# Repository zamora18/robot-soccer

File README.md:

Robot Soccer - Team 5: Chicken McThuggets
=========================================

#### Background

Robot Soccer is a competition held each year where teams from all over the world build robots based on motion control, artificial intelligence (AI) and strategy, computer vision, and mechanical design. These robots compete in an autonomous soccer game as regulated by two independent organizations: RoboCup and FIRA. Both organizations were founded in 1997 and have continued to gain international popularity from its fans.

The Electrical and Computer Engineering Department at Brigham Young University also hosts a smaller-scale Robot Soccer competition. This competition was built to be a senior project for undergraduates and is the amalgamation of many sub-disciplines within ECEn. This is the third iteration of this particular senior project based on the ODROID and RoboClaw motor controllers. The BYU competition requires that ten Robot Soccer teams will create two soccer-playing robots each.

#### Our Robots

  - Nugget
  - Nugget v2.0
  - Fry

#### Resources

  - [Our Wiki](https://github.com/zamora18/robot-soccer/wiki)
  - [BYU Class Wiki](http://rwbclasses.groups.et.byu.net/doku.php?id=robot_soccer:2016:start)

#### Contact

  - [Parker Lusk](https://github.com/plusk01), motion control
  - [Chris Frame](https://github.com/cwframe), vision
  - [Troy Ellis](https://github.com/robo-hobojoe), hardware
  - [Jake Zamora](https://github.com/zamora18), AI and strategy

To see what has become of us, view our [credits](https://www.youtube.com/watch?v=zJYsS5C2Bes)!

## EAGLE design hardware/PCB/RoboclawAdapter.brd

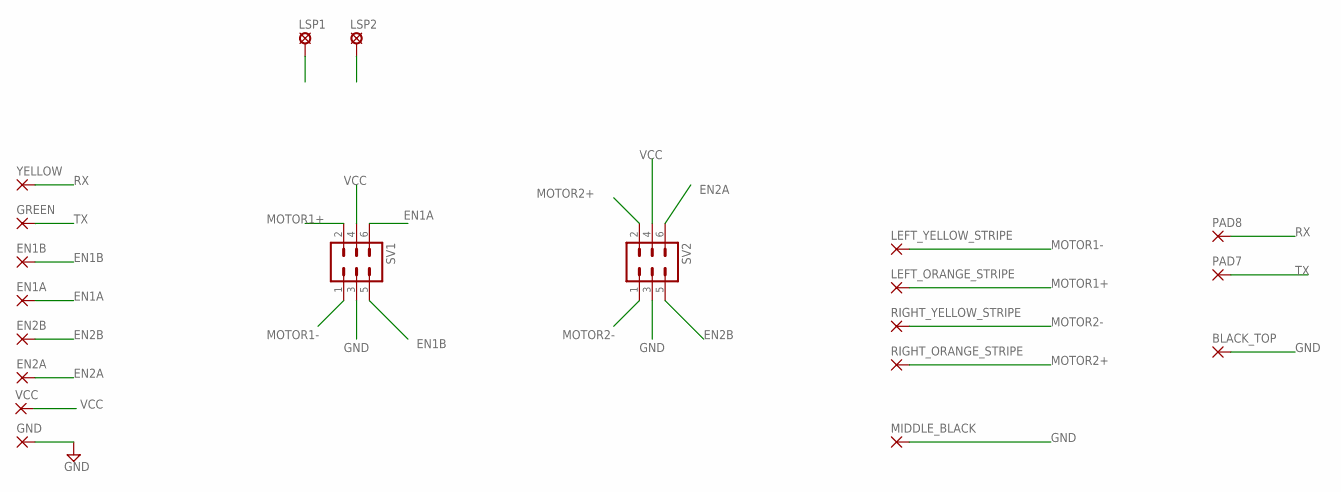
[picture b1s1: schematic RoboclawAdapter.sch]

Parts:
BLACK_TOP: 2,54/0,9
EN1A, EN1B, EN2A, EN2B: 2,54/0,9
GND: 2,54/0,9
GREEN: 2,54/0,9
LEFT_ORANGE_STRIPE: 2,54/0,9
LEFT_YELLOW_STRIPE: 2,54/0,9
LSP1, LSP2: SE14
MIDDLE_BLACK: 2,54/0,9
PAD7, PAD8: 2,54/0,9
RIGHT_ORANGE_STRIPE: 2,54/0,9
RIGHT_YELLOW_STRIPE: 2,54/0,9
SV1, SV2: MA03-2
VCC: 2,54/0,9
YELLOW: 2,54/0,9

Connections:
EN1A: EN1A.1, SV1.6
EN1B: EN1B.1, SV1.5
EN2A: EN2A.1, SV2.6
EN2B: EN2B.1, SV2.5
GND: BLACK_TOP.1, GND.1, MIDDLE_BLACK.1, SV1.3, SV2.3
MOTOR1+: LEFT_ORANGE_STRIPE.1, SV1.2
MOTOR1-: LEFT_YELLOW_STRIPE.1, SV1.1
MOTOR2+: RIGHT_ORANGE_STRIPE.1, SV2.2
MOTOR2-: RIGHT_YELLOW_STRIPE.1, SV2.1
RX: PAD8.1, YELLOW.1
TX: GREEN.1, PAD7.1
VCC: SV1.4, SV2.4, VCC.1
VCC12: LSP1.MP, LSP2.MP

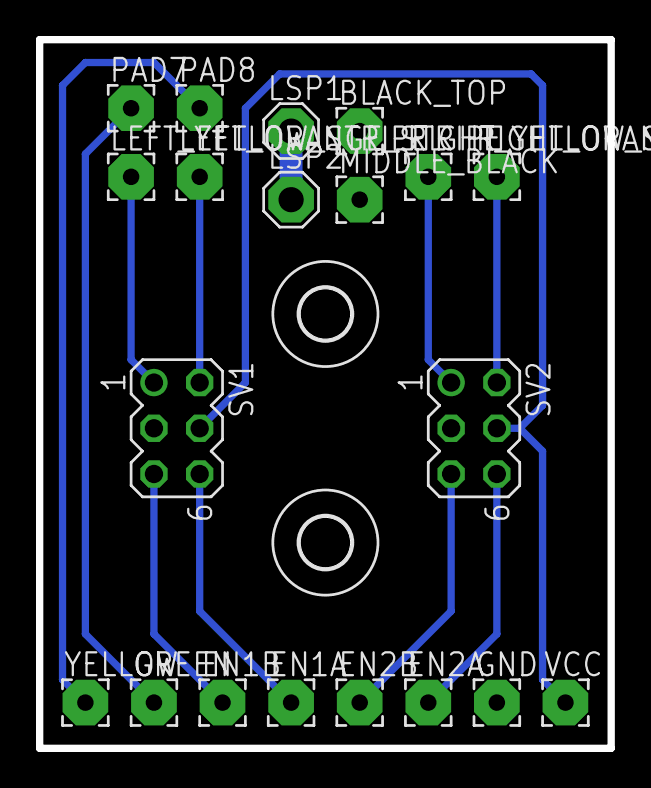
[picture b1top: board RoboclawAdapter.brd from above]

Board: 2 copper layers, 31.8 x 39.4 mm, 22 parts (0 on the bottom side), 13 nets.

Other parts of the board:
U$1, U$2: 2,8

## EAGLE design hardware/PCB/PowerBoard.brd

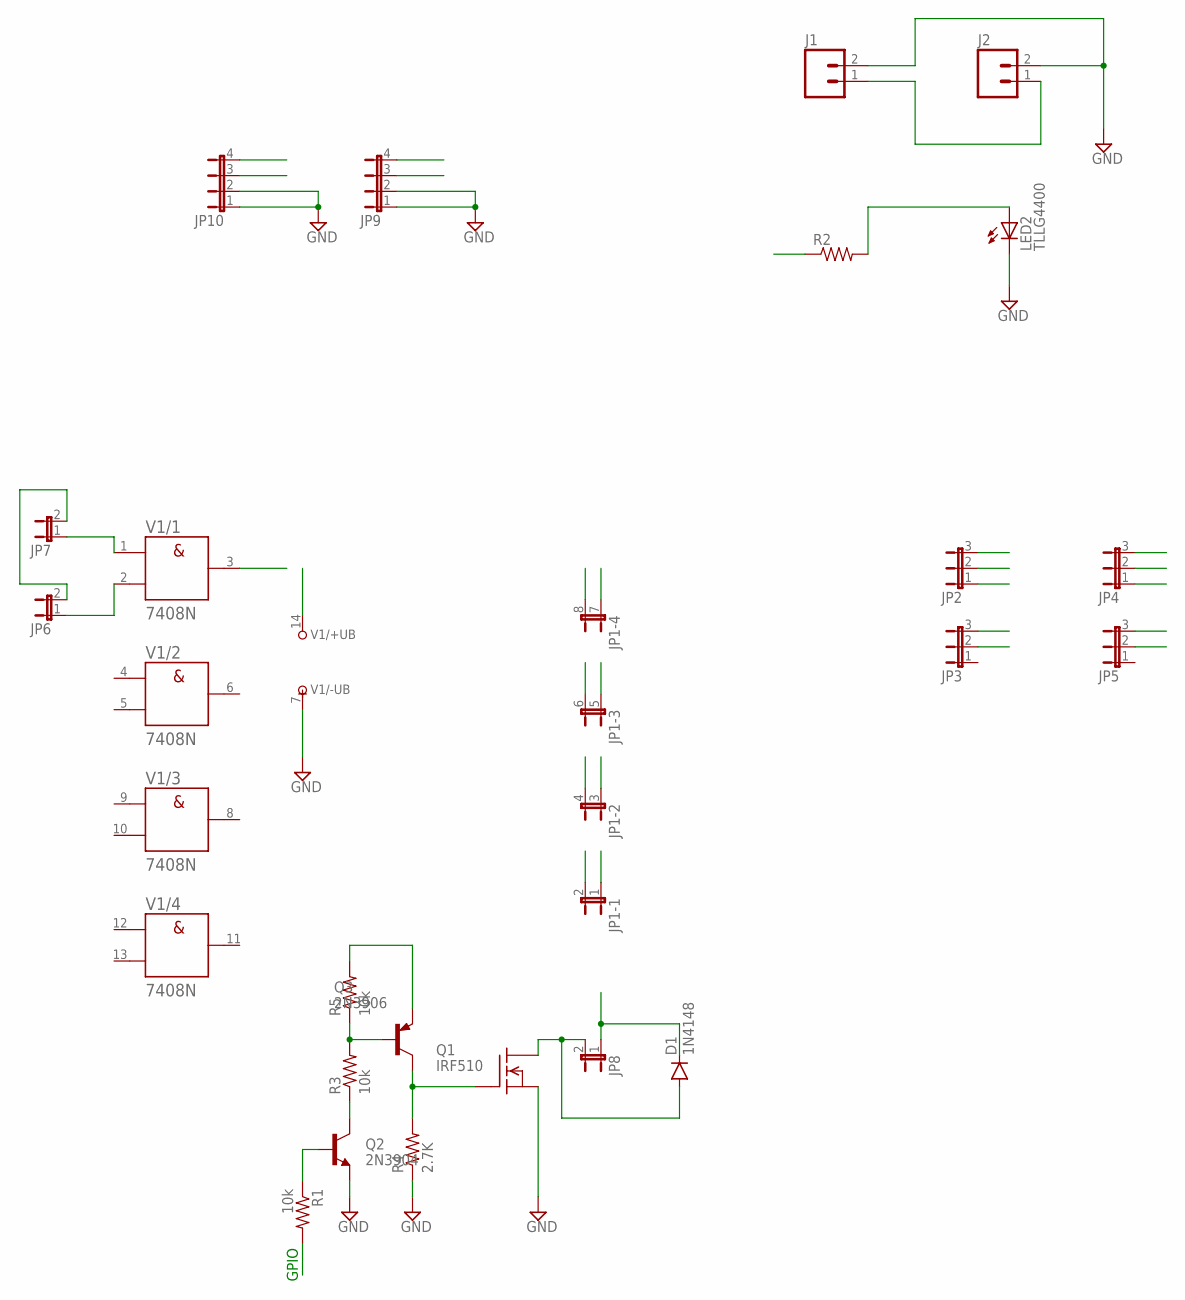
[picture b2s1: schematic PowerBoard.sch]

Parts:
D1: 1N4148; DIODE-1N4148
J1, J2: M02JST-PTH-2; JST-2-PTH
JP1: JP4QE; JP4Q
JP2, JP3, JP4, JP5: JP2E; JP2
JP6, JP7, JP8: JP1E; JP1
JP9, JP10: JP4E; JP4
LED2: TLLG4400; LED3MM
Q1: IRF510; TO220
Q2: 2N3904; TO-92
Q3: 2N3906; TO92
R1, R3, R5: 10k; AXIAL-0.4
R2: RESISTORPTH-1/4W; AXIAL-0.4
R4: 2.7K; AXIAL-0.4
V1: 7408N; DIL14

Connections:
1.8VCC: JP1.3 (1), JP2.1
5VCC: JP1.7 (1), JP4.1, JP10.3, R2.P$1 (1), V1.14 (+UB)
15VCC: D1.C, J1.1, J2.1, JP8.1, JP9.3, Q3.3 (E), R5.P$2 (2)
ANDIN2: JP6.1, V1.2 (B)
FLOAT1: JP1.8 (2)
FLOAT2: JP1.6 (2)
FLOAT3: JP10.4
FLOAT4: JP9.4
GND: J1.2, J2.2, JP1.5 (1), JP3.3, JP5.3, JP9.1, JP9.2, JP10.1, JP10.2, LED2.K (C), Q1.3 (S), Q2.1 (E), R4.P$1 (1), V1.7 (-UB)
GPIO3: Q2.2 (B), R1.P$1 (1)
HV1: JP4.3, JP6.2, JP7.2
HV2: JP4.2, V1.3 (Y)
HV3: JP5.2
KICKER: JP1.4 (2), R1.P$2 (2)
LV1: JP1.1, JP2.3
LV2: JP1.2, JP2.2
LV3: JP3.2
unnamed: Q2.3 (C), R3.P$1 (1)
unnamed: Q3.2 (B), R3.P$2 (2), R5.P$1 (1)
unnamed: D1.A, JP8.2, Q1.2 (D)
unnamed: Q1.1 (G), Q3.1 (C), R4.P$2 (2)
unnamed: JP7.1, V1.1 (A)
unnamed: LED2.A, R2.P$2 (2)

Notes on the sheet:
GPIO

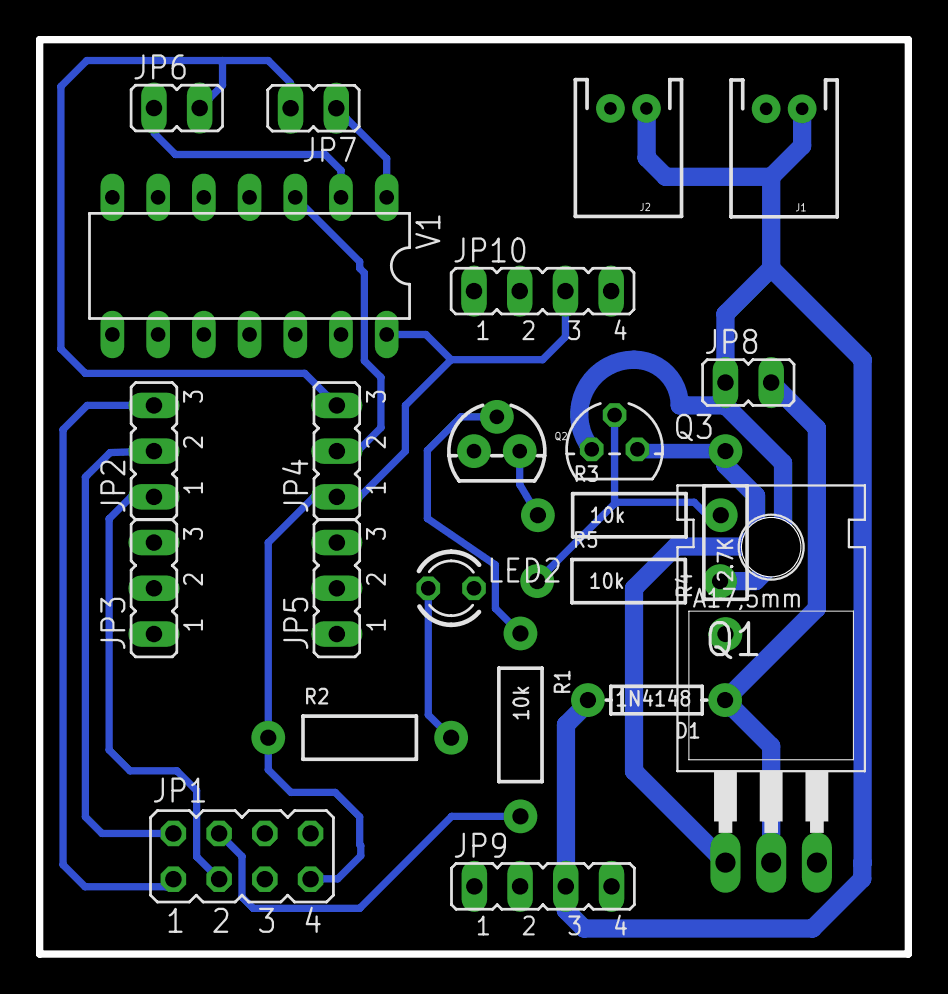
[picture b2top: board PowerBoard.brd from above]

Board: 2 copper layers, 48.3 x 50.8 mm, 23 parts (0 on the bottom side), 17 nets.

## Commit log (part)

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2016-03-05 changed MATLAB gui axis; found measurement flag error in estimator
2016-03-05 process ball data with vision
2016-03-08 new periodic spin controller code
2016-03-08 chris is pushing for parker when he went to reception things
2016-03-08 controller changes
2016-03-08 changed tolerance; remove controller shut off in node
2016-03-08 agressive defense
    added agressive defense, it follows the ball but doesnt attack
2016-03-08 cos is giving the opposite of what we expect
2016-03-08 minor changes
    hahaha
2016-03-08 arctan2
    HAPPY PARKER?!?!?!?!!?!?!
2016-03-08 got things moving!
2016-03-08 ip address
2016-03-08 MATLAB go to point with angle
2016-03-08 set up kick
    added skill to set up kick and a function that calculates points for us
    for triangles
2016-03-08 defends goal in arc
    defends in arc
2016-03-08 changes to arc defense
    some changes were made
2016-03-09 can now do away and home by pressing 'a' and 'h'
2016-03-09 can push all the buttonz
2016-03-09 added approach to the ball for kick, nnot reliable
2016-03-09 fixed close on setup
    now computes close differently
2016-03-09 changed tolerances
    see above
2016-03-09 changed 3 to 3.0
2016-03-09 Still working on strategy and plays
2016-03-09 about to test simple ai with kicker
2016-03-09 what happened?
2016-03-09 forgot iterable
2016-03-09 more
2016-03-09 almost working
2016-03-09 working on guidedog
2016-03-09 added edge padding
2016-03-09 added vision ally position
2016-03-09 fixing guidedog and changing tolerances
2016-03-09 fixed away code when something was hiding
2016-03-09 added goal teller
2016-03-09 this is probably right
2016-03-09 rushes ball if closer on def
    see above
2016-03-09 return it, chris!
2016-03-10 vision from competition, at least one thing chris did worked.
2016-03-10 lost
2016-03-10 fixed compettition bug, nnot tested
    above
2016-03-10 added walle's gazebo code, renamed soccersim, vision not working
2016-03-11 remove search for msg folder in soccersim
2016-03-11 added kicker to robot xacro, tried to make ball stop when clicked down
2016-03-11 got step responses working
2016-03-11 MATLAB fixes
2016-03-11 Organized files, created Constants.py and Utilities.py. Not completely done though
2016-03-12 cleaned up step response code and graph
2016-03-12 don't window theta error
2016-03-12 changing PID constants
2016-03-12 matlab stuff
2016-03-12 playing with windowing theta error
2016-03-12 fixed the gazebo vision to pass degrees instead of radians
2016-03-12 tweaking windowed error size
2016-03-13 Added to files, working on Skills
2016-03-14 syntax garbage
2016-03-15 first draft implementation of opponent Kalman filter
2016-03-15 syntax and matrix things
2016-03-15 implemented mdiv
2016-03-15 switching row vectors for col vectors
2016-03-15 stupid MATLAB 1-based indexing
2016-03-15 connected up robot state
2016-03-15 added robot estimation to launch file; changed Q matrix
2016-03-15 now you can see the thresholds by pressing 1 2 3 4 and 5, maker sure to press it again to turn it off or else it will get behind, also the lame blue is now bc, and the vibrant blue is b
2016-03-15 playing with Q noise statistics
2016-03-15 trying to abstract out LPF
2016-03-15 tuning LPF for ball estimator
2016-03-15 fixes
2016-03-15 simple seems to work better than delay
2016-03-15 trying to clean things up
2016-03-15 more estimation clean up
2016-03-15 things
2016-03-15 Basically done with organizational changes, and utility functions.
2016-03-15 more data
2016-03-15 trying to add simulator kick
2016-03-15 purple
2016-03-15 doesnt get stuck behind ball anymore on aggressive offense
2016-03-15 making a service call robot estimator to toggle it
2016-03-16 trying to get this to owrk
2016-03-16 pub global
2016-03-16 robot chases infront of ball
2016-03-16 robot now doesnt freeze at all in simulator and does correct things
2016-03-16 hack node
2016-03-16 took robot estimation out and replaced with hack node
2016-03-16 fixed a small issue with the returning to home
2016-03-16 tried to abstract out kick
2016-03-16 changed angles of shots and tolerance on theta for shots
2016-03-16 syntax fix
2016-03-16 trick playz
2016-03-16 haaandddss
2016-03-16 guidedog
2016-03-16 triiiick shooooottt
2016-03-16 fix MATLAB thing
2016-03-16 trick shot
2016-03-16 competition
2016-03-16 Minor changes after the 1v1 competition
2016-03-18 fixed some hsv values and 1 bug
2016-03-18 syntax
2016-03-19 MATLAB estimation reruns
2016-03-19 added comments
2016-03-19 right before adding a branch
2016-03-19 I'm trying!
2016-03-19 uhh..
2016-03-19 add fry launch
2016-03-19 MATLAB with ally1 ns
2016-03-19 making new functions to make everything more clear
2016-03-19 hooking up ROS
2016-03-20 trying to make SetBool happy
2016-03-20 remap guidedog stuff
2016-03-20 changed estimator
2016-03-20 MATLAB
2016-03-22 trying to make the simulation world easier
2016-03-22 Making our code look clean. Taking a while.... So far we only have goalie functionality
2016-03-22 added kapal's A* implementation and added some matplotlib test code
2016-03-22 Getting headway on 2v2 code. Now have goalie, defender, and some attacker functionality for both robots
2016-03-23 finds a path with no obstacles but not optimal path, doesnt use diagonals
2016-03-23 correctly uses diagonals to do real things
2016-03-23 I really hope this code works
2016-03-23 I suck at git
2016-03-23 Prepping to run in the simulator
2016-03-23 teleop calibration fix
2016-03-23 words
2016-03-23 NO MORE SYNTAX ERRORS
2016-03-23 try thios
2016-03-23 trying to figure out stuff with simulator
2016-03-23 Coin toss to whether this even works
2016-03-23 Fixed last syntax errors, ideally should be ready for 2v2
2016-03-24 Uncommitted changes on linux? I didn't think I did...
2016-03-25 implemented 1v1 functionality. Tested in simulator, but simulator is having its issues. Still no 2v2 functionality in simulator.
2016-03-25 Finally should have a good shooting function. Worked well in the simulator. Some other weird things are happening though. Needs more testing
2016-03-26 two robot simulator
2016-03-26 Minor updates from the last time
2016-03-26 can find path, but takes to long to run
2016-03-26 2v2 SHOULD be done, with no syntax errors. May have to commit one more time :)
2016-03-26 Having weird return None errors. Trying to figure it out
2016-03-26 Resolved None type error. Attacker function being weird on 2v2 though
2016-03-26 removed old vision code
2016-03-26 restructuring launch files
2016-03-26 deleted ROS scripts folder
2016-03-26 update odroid setup bash
2016-03-27 broke out ally positions from YAML
2016-03-27 thats embarassing
2016-03-27 renamed a lot of things from robot to ally1 and robot2 to opp1 to make it easier to implement ally2 and opp2, have not yet changed node names yet, for fear of breaking things
2016-03-27 reduced wind up time on startup
2016-03-27 now refactored, inits colors more cleanly and easier to adjust colors, they are found in the visionobject.cpp under initcolor.
2016-03-27 vision now in center of robot
2016-03-27 catkin fix:
2016-03-27 Should be good for playing 2v2 and 1v1. Added some protection against hitting walls, but wasn't able to test it. Also added code for staying a certain distance away from each other (teammates)
2016-03-27 motion doesn't complain anymore; added simulator setup script; added requirements with roboclaw-v3 pip install requirement
2016-03-27 script dir
2016-03-30 Parker helped me with some simulator stuff. I semi-fixed the problem of shooting towards our goal when on defense. Still needs some work
2016-03-30 Fixed defensive strategy. Implemented an 'avoid own goal' when the ball is behind the robot. Still working out some kinks, but in most cases it avoids kicking it in our own goal. Other than that, 1v1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
2016-03-31 There are some problems I found with the simulator. It does not recognize ally1 so it is doing weird things. I'll get back to it later.
2016-03-31 fixed i think; realizing that this needs to be a python pyQt thing, not MATLAB because of all the ROS callbacks...
2016-03-31 that's embarrassing... fixed the robots identity crises
2016-03-31 Before Parker fixed his mistakes in the simulator
2016-03-31 Little fixes... Still doing own goal crap. Can't figure it out..
2016-04-01 gui with matplotlib
2016-04-01 added kick button
2016-04-01 hooked up battery button
2016-04-01 velocity vector plots, more or less
2016-04-01 set desired position and stop moving
2016-04-01 click to drive with angle (but no line) complete
2016-04-01 Ready to test 2v2 code
2016-04-02 bash setup scripts change, added IP address
2016-04-04 tried to make plotting more efficient
2016-04-04 added turning off the gazebo gui arg
2016-04-05 got it to 5ms wih a separation of .067
2016-04-06 can do stuffs
2016-04-06 I'm sorry for all of my syntax errors... I'll take a paycut
2016-04-06 my first syntax error ever
2016-04-06 one v one thing
2016-04-06 Testing 1v1 to make sure it works for competition in case 2v2 goes to crap
2016-04-06 spacebar sends start, sends garbage if its 2v1
2016-04-06 game_state is a global topic
2016-04-06 start signal
2016-04-06 hands
2016-04-06 Took out dumb trick shot
2016-04-06 Ready for 1v1, took out is_stuck function because we haven't been able to test it
2016-04-07 made robot shoot more toward middle of goal
2016-04-07 first attempt at making v5 roboclaws work with our code base
2016-04-08 trying to add path planning node
2016-04-08 git dat stuff
2016-04-08 roslaunch remap reorder rrr-alliteration
2016-04-08 be explicit about not having to verify checksum
2016-04-08 get that print statement outta here!
2016-04-08 added code to read YAML file and determine if we should use rcv3 or not
2016-04-08 try this
2016-04-08 reverting some changes
2016-04-08 scripts decide which roboclaw version to use
2016-04-08 path_planning node fix
2016-04-08 script changes for rcv3
2016-04-08 took out path planning and other things
2016-04-08 nugget has a new set of wheels and roboclaws (aka QPPS values changed)
2016-04-08 change pids part 2
2016-04-08 changed field size in simulator
2016-04-08 tried to make the ball bigger so it doesn't get underneath the robot as much
2016-04-08 spacebar
2016-04-09 x is working
2016-04-09 step response done
2016-04-09 renamed to gui.py, added simulator script functions
2016-04-09 added ball state to GUI
2016-04-09 slight change
2016-04-09 fixed field size thing
2016-04-09 put PIDs in yaml
2016-04-09 hooked up PID constants from YAML config files
2016-04-09 oh, come on!
2016-04-09 avoiding instead of path planning
2016-04-09 mooooreee avoidance
2016-04-09 added desired safe for Chris
2016-04-09 Still working on the defender acting weird, but I changed the avoid_own_goal function to make it more simple. I have been working mostly on 1v1 strategy.
2016-04-09 tunning nugget
2016-04-09 guidedog listens to two opponnents?
2016-04-09 Fixed a butt ton of *ish* so now we should be able to play 2v2. De nada
2016-04-09 someone fire me
2016-04-09 ahhahah
2016-04-09 Just deleted some unwanted garbage
2016-04-09 Syntax on 2v2
2016-04-09 Making ally2 attack only on the half-field line
2016-04-10 col clean up
2016-04-10 command center change field dimensions
2016-04-11 various left over commits
2016-04-12 goalie wont avoid robots
2016-04-12 Fixed issue with attack_ball_towards_goal. Piece of crap code. my bad guys....
2016-04-12 avoid all of them
2016-04-12 guidedog doesnt care about the goal region
2016-04-12 changed padding for guidedog
2016-04-12 Added future positions to am_i_too_close_to_teammate() function.
2016-04-12 added u and t functionality for keeping track of goals
2016-04-12 Fixed problem with ally2 on offense
2016-04-12 avoid your ally and the guidedog knows if its one_v_one or not
2016-04-12 oops. removed merge conflict stuff
2016-04-12 simulator and command center niceties
2016-04-12 vision push
2016-04-12 made goalie defend crossing point
2016-04-13 working on it
2016-04-13 avoid defender hitting goalie
2016-04-13 Fixed one small thing I forgot to delete
2016-04-14 took out install dir from ROS
2016-04-14 readme stuff
2016-04-20 changed ROS readme
2016-04-20 added nodes readme
2016-09-06 created readme
    work in progress
2016-09-06 updated readme
    updated

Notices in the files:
parts and their libraries:
SparkFun-Resistors: Licensing: Creative Commons ShareAlike 4.0 International - https://creativecommons.org/licenses/by-sa/4.0
